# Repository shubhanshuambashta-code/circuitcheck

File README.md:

# CircuitCheck

Review a KiCad PCB project before sending it for fabrication. CircuitCheck runs native KiCad checks, shows each reported problem on the board, and lets you preview a supported correction in a separate copy before applying it and checking again.

## Start on Windows

Extract the ZIP completely. For a new installation, double-click **Setup CircuitCheck.cmd** once; then double-click **Start CircuitCheck.cmd** and keep its server window open. The supplied production frontend does not require Node.js during setup. Python and KiCad remain runtime prerequisites. This configured computer can reuse its existing installation through the private `data/runtime.json` file. Reopening the launcher reuses an already running matching local server.

The hosted site is an interactive recording. It supports Actions deployment at the repository URL and a committed `site/` production build when GitHub Pages serves the main branch directly. Run `npm run build:branch-pages` when updating that fallback. Source HTML automatically opens the compiled fallback; it never asks a static host to execute TypeScript.

## Engineering review v0.2.1

- The local app and public website share the same review interface. The website is an **interactive recorded example**, clearly labelled; live uploads and edits require the local engine.
- Click a finding to zoom to UUID-resolved tracks, pads, components or reported locations. Pads/components use explicit object envelopes. Net highlighting follows stored net assignments. Unavailable mappings are labelled and never guessed; schematic findings cross-probe only unambiguous matching component references/pads.
- Confirmed native rule violations, evidence-supported review suggestions and unconfirmed potential concerns are separate categories. AI explains selected evidence and does not establish engineering violations.
- Coverage lists evaluated checks, findings, ignored rules, failures, missing dependencies and checks that were not performed. There is no overall safety score. Rule/profile fingerprints, source hashes, KiCad, normalizer, geometry and explanation-engine versions are visible.
- **Upload revision B** into the current project to compare resolved, remaining and new findings, moved/changed components and physical routing/pad-net changes. Review comments and accepted exceptions persist. Exceptions retain the native finding and require re-review when their evidence or scope changes.
- Rule/profile/engine/coverage changes or unstable object identities prevent a disappearance from being labelled a verified fix. UUID rewrites appear as added/removed objects. Physical routing comparison does not infer circuit intent or establish logical connectivity equivalence.
- Select the `PCBWAY-STANDARD-BASELINE` published snapshot, import a numeric JSON profile, enter custom minimum dimensions, or include native `.kicad_dru` rules in the project ZIP. Manufacturer order references are stored as metadata; unknown codes do not fetch or invent private order constraints. Presets are scoped published minima, not full manufacturer approval.
- Supported track-width fixes follow **copy → native recheck → review → explicit approval → apply → fresh recheck → download**. Other findings show a specific manual action in KiCad and can be re-uploaded as a revision.
- Readable HTML and JSON reports retain coverage, provenance and review decisions; JSON also records explanation history and the actual explanation-model identifier returned by the provider when available.

JSON fabrication profile example (all dimensions in mm):

```json
{"code":"CUSTOM","name":"My fabrication specification","version":"1","source":"Approved drawing / quote reference","constraints":{"track_width":0.2,"clearance":0.2,"hole_size":0.3}}
```

Supported numeric constraints: `track_width`, `clearance`, `hole_size`, `annular_width`, `edge_clearance`. A separate native KiCad DRC pass evaluates these in a disposable copy while preserving the original project rules and original files.

## What it does

- Accepts a complete KiCad project ZIP or multiple native project files.
- Shows actual engine findings, reported locations, rule evidence and check coverage.
- Previews a correction for a supported straight-track width violation, then reruns native checks before apply is available.
- Preserves originals and revision history, with comparison, restore and native project export.
- Includes downloadable synthetic test projects with known expected results at `/test-files/`.
- Works without an AI key. Optional model explanations are separate from the native check results.

This is a local, single-user application. Switch between Board and Schematic to inspect native exports, select hierarchical sheets and navigate electrical-rule findings. ERC pins use native reported coordinates, symbols use labelled anchors and source wires retain their UUID paths. Revision comparison supports both board and schematic views. General schematic editing and logical net tracing remain in KiCad. The included Fieldnode design is an original synthetic test fixture, not a validated functional circuit.

## Tech stack

| Layer | Technology |
|---|---|
| Interface | React, TypeScript, Vite, Tailwind CSS |
| API | Python, FastAPI, Uvicorn |
| Analysis | Separate Python worker calling native KiCad CLI |
| Local storage | SQLite and project files |
| Tests | pytest and Playwright |

## Quick start

Clone or download this repository, open a terminal in its root, then follow the setup below. KiCad is installed separately; it is not bundled in the repository.

### Install and run

Tested host: Windows x64, Python **3.14.6**, Node **24.21.0**, npm **11.19.0**, KiCad **10.0.7**. Direct Python dependencies are pinned in `requirements.txt`; the tested full dependency set is in `requirements.lock.txt`. Frontend dependencies are pinned in `package.json` and `package-lock.json`.

1. Install Python 3.12 or later and Node 22.12 or later. Only the versions above were executed on this host.
2. Install **KiCad 10.0.7** from [the official Windows download page](https://www.kicad.org/download/windows/) or [official Linux instructions](https://www.kicad.org/download/linux/). Website visitors use the server's engine; they do not need KiCad on their own devices.
3. In this folder, run:

```powershell
.\scripts\setup.ps1
```

4. If KiCad is not found automatically, copy `.env.example` to `.env` and set its literal `KICAD_CLI` path. Leave `AI_API_KEY` empty for deterministic explanations.
5. Run `.\scripts\start.ps1`.

For Linux/macOS:

```sh
sh scripts/setup.sh
# If needed: export KICAD_CLI=/absolute/path/to/kicad-cli
.venv/bin/python scripts/start.py --open
```

Linux/macOS startup scripts are supplied but were not executed here. Do not copy the Windows CLI path from `.env.example` on Linux.

## GitHub Pages preview

The published site provides an interactive replay of two real native KiCad runs on an original synthetic fixture, with object highlighting, revision comparisons, coverage, review history and downloadable native project versions. Its persistent banner identifies recorded results. GitHub Pages cannot execute FastAPI, SQLite jobs or native KiCad; live uploads, notes and approved edits require the local application.

In **Settings > Pages**, set **Source** to **GitHub Actions**. `.github/workflows/pages.yml` installs locked frontend dependencies, runs `npm run build:pages`, and deploys only `dist-pages/`. The Pages build uses `/circuitcheck/` as its base; `npm run build` still produces the working local application in `dist/` with `/` as its base. Do not publish the source folder directly: browsers cannot execute the TypeScript entry point without Vite's build step.

To preview the Pages build locally, run `npm run build:pages`, then `npm run preview -- --mode pages --outDir dist-pages --port 4173`. Visit `http://127.0.0.1:4173/circuitcheck/`. A full public analysis deployment would additionally require a server with KiCad, worker processes, persistent storage, authentication, project ownership checks and isolated execution; none is provisioned by this workflow.

## Development and tests

The API and worker must both run. From this folder, with the Python environment activated:

```sh
python -m uvicorn backend.main:app --host 127.0.0.1 --port 8000
python -m backend.worker
npm run dev
```

Vite serves port 5173 and proxies `/api` to port 8000. For production local use, `npm run build` produces `dist/`, which FastAPI serves directly. Interactive API documentation is at `/docs`.

```sh
python -m pytest -q
npm run build
npm run test:e2e
```

Browser tests use an installed Chrome by default. Set `PW_CHANNEL=msedge` to use Edge, or install the matching Playwright Chromium and use the appropriate channel configuration. Set `PW_BASE_URL=http://127.0.0.1:5173` when testing the Vite server. Run the API and worker before browser tests. They intentionally create synthetic projects in the configured data directory; use a disposable `CIRCUITCHECK_DATA` directory for an isolated test installation.

Fixtures are original, redistributable CC0 content. `scripts/generate_fixtures.py` regenerates them with deterministic UUIDs. Tests use real KiCad for clean boards, deliberate DRC/ERC findings, SVG coordinate checks, hierarchical schematics, custom rules, missing libraries, repair validation, comparisons and downloads. Engine tests skip explicitly if KiCad is absent; a skipped integration is not a pass.

See `VERIFICATION.md` for executed checks, results and remaining limitations. Rendered examples are in `screenshots/`.

## Review workflow

### Try it without your own design files

Open `http://127.0.0.1:8000/test-files/` while CircuitCheck is running. This page provides downloadable native KiCad ZIPs, literal expected results, original engine reports and a step-by-step repair test. Upload each ZIP unchanged. The deliberate width problem reports 1 error and 1 unconnected-end warning; the corrected width reports 0 errors and the same warning; the empty board outline reports no DRC findings. These are synthetic fixtures, and no schematic is checked in those three cases. The downloadable cases were also executed through the live upload/worker pipeline after packaging.

1. Upload a complete project ZIP, or select multiple native files together. ZIPs preserve hierarchy and directory structure. Originals are stored separately.
2. Select a root only when multiple independent candidate roots exist. The worker runs supported checks outside the upload request.
3. Select a finding in the table or viewer. Reported coordinates, objects, rules and literal measurements appear in the details panel. Location is left unavailable when the engine does not provide one.
4. For a supported track-width violation, select **Preview change**. Only the exact segment UUID's width atom is changed in a new candidate copy. The engine reopens it through SVG export and reruns DRC before apply is available.
5. Review resolved, remaining and new findings. **Apply change & recheck** creates the current revision and runs fresh checks. A saved file or a lower total finding count does not establish a verified resolution.
6. Use Revisions to compare or restore the parent revision. Export originals, the current native project ZIP, or the normalized JSON report. Original engine JSON, logs, SVG exports and the schematic netlist remain available through project-scoped artifact routes.

The viewer uses native full-page, scale-1, unmirrored SVG exports. Mapping comes from millimetre dimensions and `viewBox`, preserving KiCad's top-left origin (X right, Y down). The native fixture endpoint-to-SVG transformation is integration-tested. Fitted/cropped SVGs and unknown coordinate mappings are not assumed. PCB layers are exported individually with identical validated transforms. Markers highlight reported positions, not inferred minimum-distance collision points. SVG element IDs are never treated as CAD object IDs.

Keyboard: Ctrl/Command+O opens upload; F fits the view; Alt+drag pans; Escape closes dialogs. Narrow screens use Design / Findings / Details tabs. Dialogs use native modal focus trapping. Reduced-motion preferences are respected.

## Capability matrix

| Input | Read | Preview | Electrical / connectivity | Geometry / manufacturing | Editing | Native export | Conversion |
|---|---|---|---|---|---|---|---|
| `.kicad_pcb` | Native | SVG layers | PCB connectivity DRC; parity with a complete matching schematic | Native project DRC | One selected straight segment's width | Revised board in project ZIP | None |
| `.kicad_sch` + internal hierarchy | Native | SVG sheets | ERC + XML netlist | Not applicable | Unavailable | Original schematic preserved | None |
| `.kicad_pro`, `.kicad_dru`, library tables and bundled native libraries | Project dependencies | Through the design | Rules and dependencies used by native checks | Native rules | Settings/rules never weakened | Preserved | None |
| Project ZIP | Validated extraction | Contained native designs | As above | As above | As above | Directory structure preserved | None |
| STEP/WRL accompanying a project; PDFs/images | Stored reference/dependency files | Not analyzed or displayed | Not checked | Not checked | Unavailable | Preserved in ZIP | None |
| EasyEDA, EAGLE, Altium, Gerber/Excellon, standalone STEP/IGES, DXF, STL | Unsupported | Unsupported | Not checked | Not checked | Unsupported | Unsupported | None |

The adapter boundary is `backend/engine.py`, with independent capabilities in `/api/capabilities`. Future formats require verified parsers/converters, fixtures and their own analysis implementation before becoming available. KiCad's broader import options are intentionally not advertised as CircuitCheck support.

A project settings file alone cannot be analyzed. Photographs, PDFs, mechanical models and fabrication plots do not establish authoritative electrical connectivity. ERC/DRC do not establish component ratings, current capacity, physical soldering quality, or functional/safety performance.

## Analysis semantics

- CLI command help is probed before using version-dependent flags. Tested pin: **10.0.7**; other 10.0 patch versions are accepted but unverified. Other major versions fail explicitly.
- Native JSON reports retain severity settings and exclusions. Exit 5 means reported violations, not an execution failure. Other nonzero exits, timeouts and malformed reports fail the affected check.
- Board DRC refills zones in memory in a disposable working copy with `--refill-zones`, without `--save-board`. SVG exports use `--check-zones`. Existing saved fills and originals are not rewritten.
- Job states: queued, running, completed, partial, failed. Completed means the applicable checks finished; absent design types remain visibly **Not checked**. Missing settings/libraries mark analysis partial. A hierarchy missing required subsheets skips ERC and cannot become a clean result.
- A native engine can sometimes read an unexpected file version. Compatibility is established by actual loading/checking/exporting; unsupported syntax fails with retained logs. CircuitCheck does not claim all historical or future native versions are verified.
- A missing custom-rule file cannot always be distinguished from a project that never had one. The upload records that uncertainty instead of inventing rules. Bundle the complete project to establish rule completeness.
- Analysis caches include content, rules, engine version, selected root and analysis options. Edits invalidate the cache. Apply forces a fresh run. Each original engine report, tool version, revision hash, rules fingerprint, logs and check coverage is retained.
- Stable finding IDs derive from engine, root file, rule, sheet and affected UUIDs. This supports comparisons for unchanged objects; rewriting UUIDs in an external editor appears as removed/new findings. Different reports referring to the same rule and exact UUID set may be coalesced; original reports preserve the complete engine output.
- Core checks do not require AI credentials. Optional AI never writes files or chooses executable operations. Free-form prose cannot be proven true automatically: schemas, known-reference checks and a conservative numerical guard reject unsupported output, and model explanations are labelled for review against evidence.

## Optional assistant

Set `AI_API_KEY`, `AI_BASE_URL` and `AI_MODEL` server-side. The adapter accepts an OpenAI-compatible `/chat/completions` endpoint with strict JSON-schema output. The default example model is `gpt-4.1-mini`; choose a model/provider that supports the same response format. See [official Structured Outputs documentation](https://developers.openai.com/api/docs/guides/structured-outputs).

Only the selected finding's evidence, rule, affected objects, known repair, identifiers and the user's question are sent. Entire project files and credentials are not sent. Network/provider failures, refusals, unknown references, schema failures and added numerical claims fall back to deterministic source evidence. No live paid model call was executed on this host because no key was configured. Validation and fallback behavior are tested.

## Storage, limits and deployment

`data/circuitcheck.sqlite3` stores projects, immutable revisions, jobs, normalized findings/results and repair previews. `data/projects/<uuid>/original/` preserves uploads; `revisions/<uuid>/source/` holds immutable native files; `artifacts/` holds reports and previews. `LocalStorage` is a storage protocol implementation and `db.py` is a small data-access layer. PostgreSQL/object storage would require a new implementation; they are not included.

Uploads are limited to 25 MB compressed, 100 MB expanded, 500 entries and 12 archive path levels. Traversal, absolute/drive/UNC names, links, platform device names, collisions, encrypted entries and nested archives are rejected. Only allowed data files are accepted. External library URIs are blocked; bundle libraries using `${KIPRJMOD}`. Uploaded scripts are never executed and dependencies are never downloaded automatically. SVG is parsed with defusedxml and reduced to a safe drawing subset, then loaded as an image with a restrictive response CSP.

Only one native job runs at a time across workers; the queue is bounded. CLI calls use argument arrays, a timeout, stripped credential variables and captured output. Windows Job Objects cap each engine process at 1.5 GiB and terminate its descendants on close. Unix processes have CPU/address-space/output-file limits. A failure to establish Windows limits fails the engine explicitly. A stale running job fails after 10 minutes without a stage update; rerun it after restarting the worker.

**Local-only deployment:** API binding is loopback, accepted Host/Origin values are local, and mutations require a custom header. This is not multi-user authentication or an operating-system security sandbox. Native local jobs still run with the launching user's OS access. Use a dedicated OS account/container for untrusted projects. This build must not be exposed publicly without authentication, ownership checks and protected per-user downloads.

Docker/Compose files are supplied with loopback port binding, a non-root user, resource caps, dropped capabilities, read-only root filesystems and a network-disabled worker. Build/run:

```sh
docker compose up --build
```

**Docker was not installed on this host, so neither image build nor Compose execution was verified.** The recipe requests KiCad upstream 10.0.7 from the official KiCad Ubuntu PPA and checks its version; it fails rather than silently installing another engine version if that package is no longer available. Container isolation and Linux limits require verification on the target host.

Project deletion removes its SQLite records and local artifacts after active jobs finish. Canceled repair previews remain in revision history until project deletion; automatic retention/garbage collection is not implemented. Back up the data directory before external maintenance.

## Troubleshooting

| Message | Action |
|---|---|
| KiCad CLI unavailable | Install 10.0.7 on the server and set the absolute `KICAD_CLI` path. No fabricated checks are substituted. |
| Cannot reach the local server / Failed to fetch | Start `Start CircuitCheck.cmd`, keep its window open, then refresh `http://127.0.0.1:8000/`. The frontend cannot upload while the backend is stopped. |
| Worker is queued indefinitely | Start `python -m backend.worker` using the same environment and data directory as the API. |
| Missing settings / library / subsheet | Upload a complete project ZIP. Review the exact missing path in check coverage. |
| Several root projects | Choose the intended root in the project selection control. |
| Source changed after preview | Upload/recheck the actual current files, then create a fresh preview. |
| Analysis failed | Review check coverage and retained `*.log` artifacts; use Rerun checks after correcting the cause. |
| Automatic repair unavailable | Apply the specific correction in KiCad and upload a new project. No suppression or rule weakening is performed. |
| npm / Python install blocked | Grant network access to official package registries and retry setup. Existing installations need not be overwritten. |

The build host's default sandbox temp directory denied pip writes; setup uses a workspace-local temp directory. KiCad was extracted from the officially signed installer without a system installation. The host sandbox disallowed KiCad's optional HKCU preferences key; those warnings were retained in logs and the actual CLI checks/exports still completed with valid reports.

## Engine references

- [KiCad 10.0 CLI](https://docs.kicad.org/10.0/en/cli/cli.html): checked against runtime command help.
- [Native PCB S-expression format](https://dev-docs.kicad.org/en/file-formats/sexpr-pcb/): the narrow concrete-syntax track editor preserves all unrelated bytes.
- [Official Windows package](https://github.com/KiCad/kicad-source-mirror/releases/download/10.0.7/kicad-10.0.7-x86_64.exe): Authenticode status **Valid**, signer **KICAD SERVICES CORPORATION**. Locally computed SHA-256: `ce3881b6a9188eb34ac1ebaaec7651149e8a025206410addfb11a1a9656ecf95`.

## License

Original application code is licensed under the [MIT License](LICENSE). Original synthetic design fixtures use [CC0 1.0](fixtures/LICENSE.txt). Third-party dependencies, including the separately installed KiCad engine, retain their own licenses. Local uploads, database contents, installed dependencies and presentation files are not part of this source repository.

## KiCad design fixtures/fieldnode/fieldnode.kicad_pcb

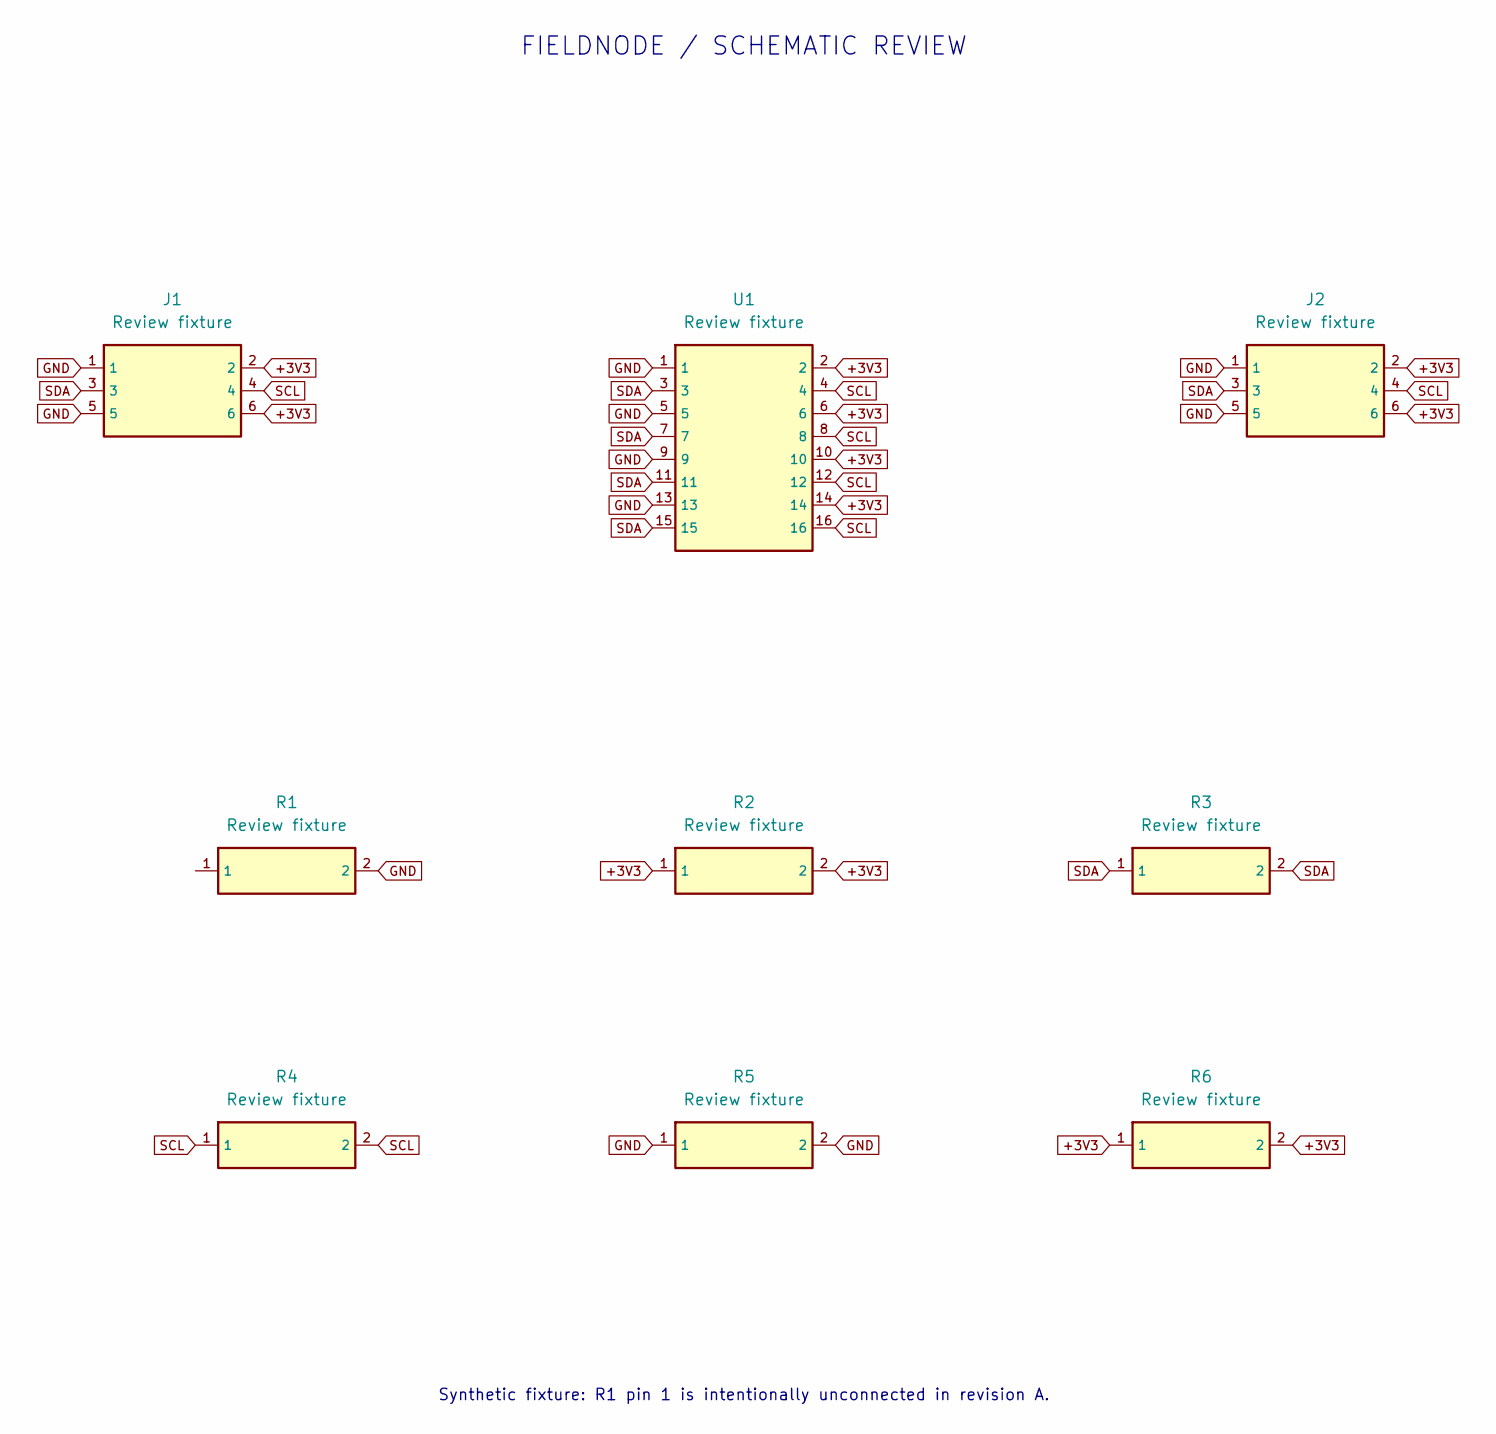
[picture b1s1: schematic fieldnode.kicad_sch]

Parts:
J1: Review fixture; J1
J2: Review fixture; J2
R1: Review fixture; R1
R2: Review fixture; R2
R3: Review fixture; R3
R4: Review fixture; R4
R5: Review fixture; R5
R6: Review fixture; R6
U1: Review fixture; U1

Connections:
+3V3: J1.2, J1.6, J2.2, J2.6, R2.1, R2.2, R6.1, R6.2, U1.2, U1.6, U1.10, U1.14
GND: J1.1, J1.5, J2.1, J2.5, R1.1, R1.2, R5.1, R5.2, U1.1, U1.5, U1.9, U1.13
SCL: J1.4, J2.4, R4.1, R4.2, U1.4, U1.8, U1.12, U1.16
SDA: J1.3, J2.3, R3.1, R3.2, U1.3, U1.7, U1.11, U1.15

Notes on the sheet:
FIELDNODE / SCHEMATIC REVIEW
Synthetic fixture: R1 pin 1 is intentionally unconnected in revision A.

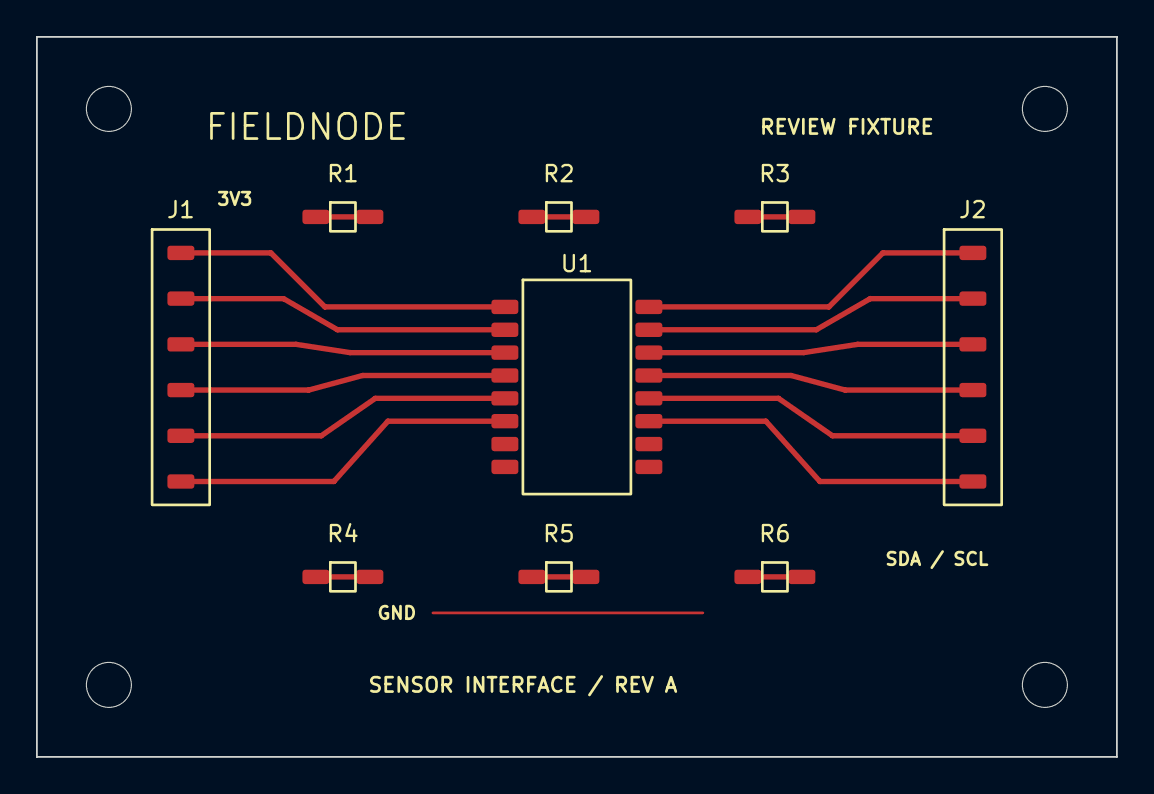
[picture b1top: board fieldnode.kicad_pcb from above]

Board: 2 copper layers, 60.0 x 40.0 mm, 9 parts (0 on the bottom side), 4 nets.
